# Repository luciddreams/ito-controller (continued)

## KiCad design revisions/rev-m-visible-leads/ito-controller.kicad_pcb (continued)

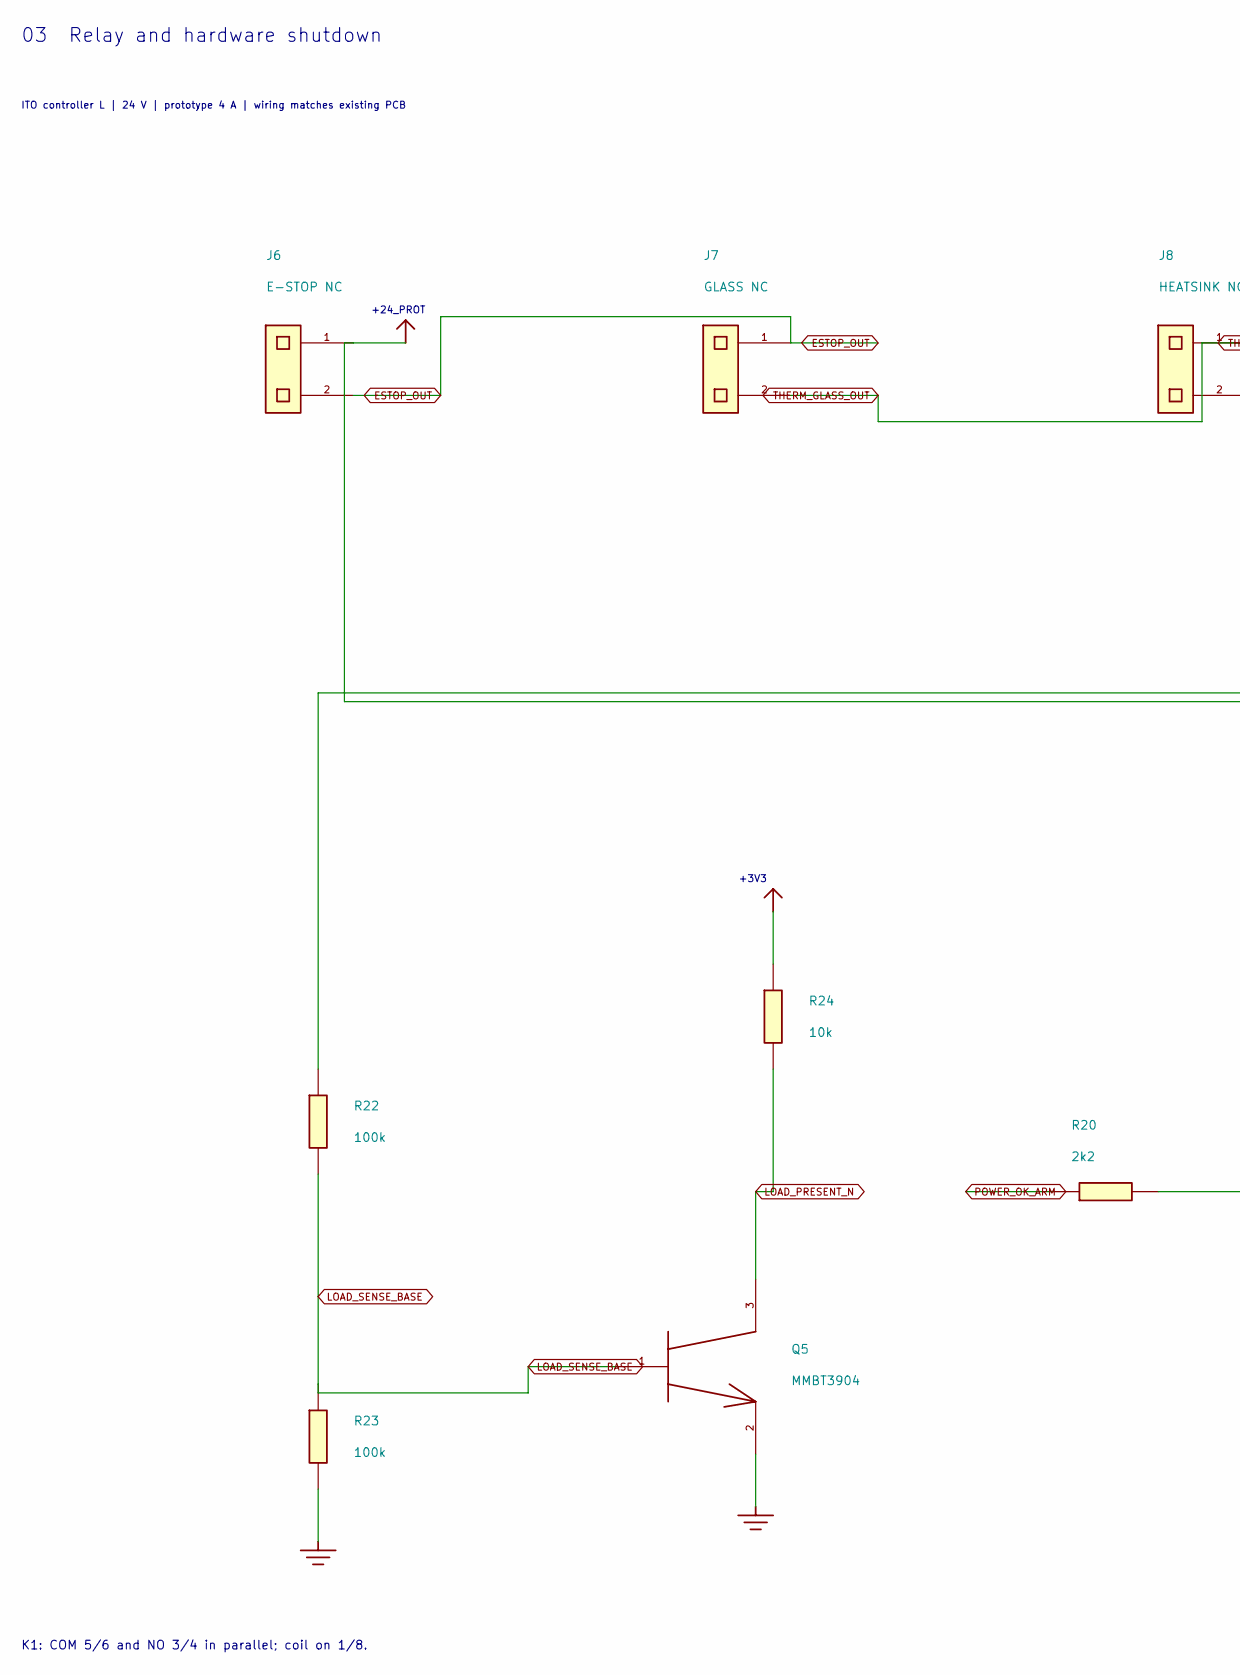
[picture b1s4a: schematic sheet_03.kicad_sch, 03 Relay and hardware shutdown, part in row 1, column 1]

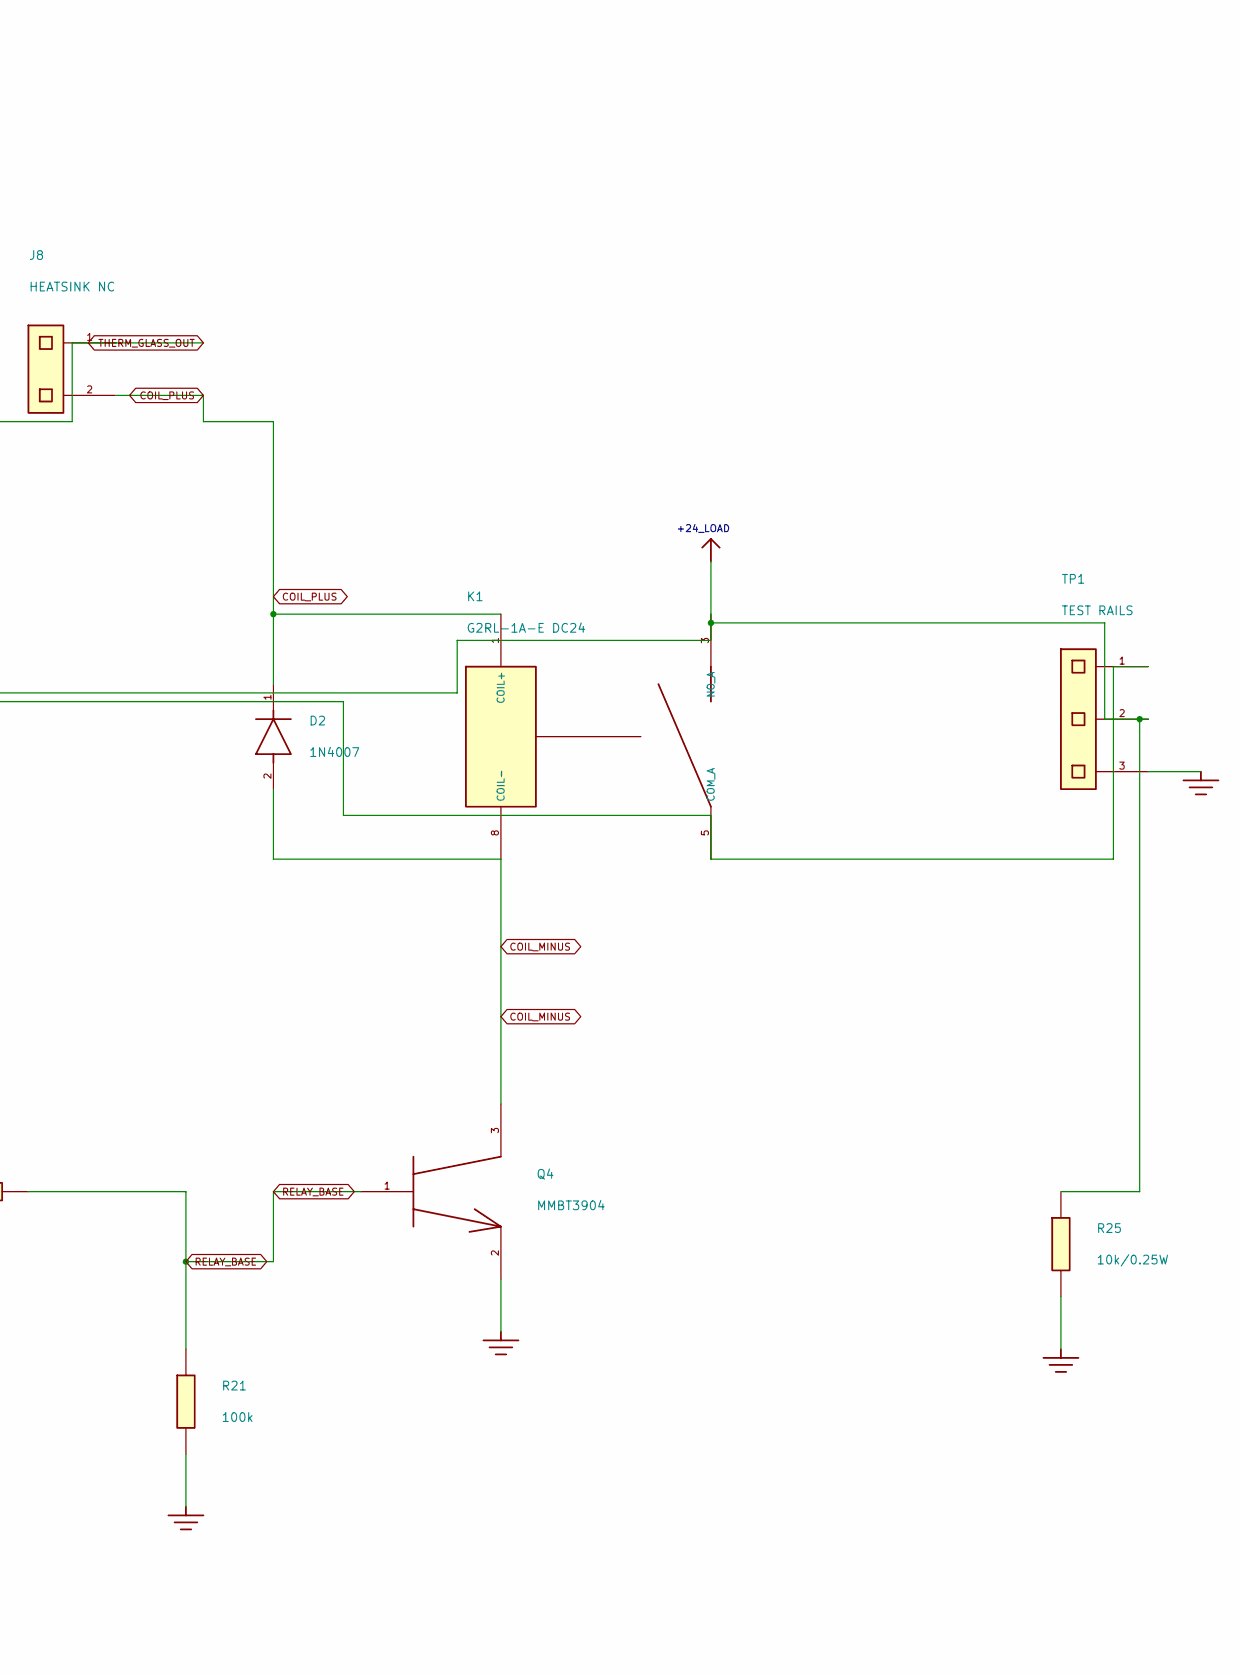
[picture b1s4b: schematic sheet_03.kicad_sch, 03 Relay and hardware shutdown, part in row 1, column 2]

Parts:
D2: 1N4007; D_DO-41_SOD81_P10.16mm_Horizontal; MPN 1N4007-E3/54
J6, J7, J8: Connector 2 pins; JST_XH_B2B-XH-A_1x02_P2.50mm_Vertical; MPN B2B-XH-A(LF)(SN)
K1: G2RL-1A-E DC24; G2RL_1A_E_review; MPN G2RL-1A-E DC24
Q4, Q5: MMBT3904; SOT-23; MPN MMBT3904LT1G
R20: 2k2; R_0805_2012Metric; MPN RC0805FR-072K2L
R21, R22, R23: 100k; R_0805_2012Metric; MPN RC0805FR-07100KL
R24: 10k; R_0805_2012Metric; MPN RC0805FR-0710KL
R25: 10k / 0.25W; R_0805_2012Metric; MPN ERJP06F1002V
TP1: Connector 3 pins; PinHeader_1x03_P2.54mm_Vertical; MPN TSW-103-07-G-S

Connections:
+3V3: R24.1; also elsewhere on the board
+24_LOAD: K1.3 (NO_A), K1.4 (NO_B), R22.1, R25.1, TP1.2; also elsewhere on the board
+24_PROT: J6.1, K1.5 (COM_A), K1.6 (COM_B), TP1.1; also elsewhere on the board
COIL_MINUS: D2.2, K1.8 (COIL-), Q4.3
COIL_PLUS: D2.1, J8.2, K1.1 (COIL+)
ESTOP_OUT: J6.2, J7.1
GND: Q4.2, Q5.2, R21.2, R23.2, R25.2, TP1.3; also elsewhere on the board
LOAD_PRESENT_N: Q5.3, R24.2; also elsewhere on the board
LOAD_SENSE_BASE: Q5.1, R22.2, R23.1
POWER_OK_ARM: R20.1; also elsewhere on the board
RELAY_BASE: Q4.1, R20.2, R21.1
THERM_GLASS_OUT: J7.2, J8.1

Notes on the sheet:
K1: COM 5/6 and NO 3/4 in parallel; coil on 1/8.
+24_PROT
+24_LOAD
+3V3
03 Relay and hardware shutdown
ITO controller L | 24 V | prototype 4 A | wiring matches existing PCB

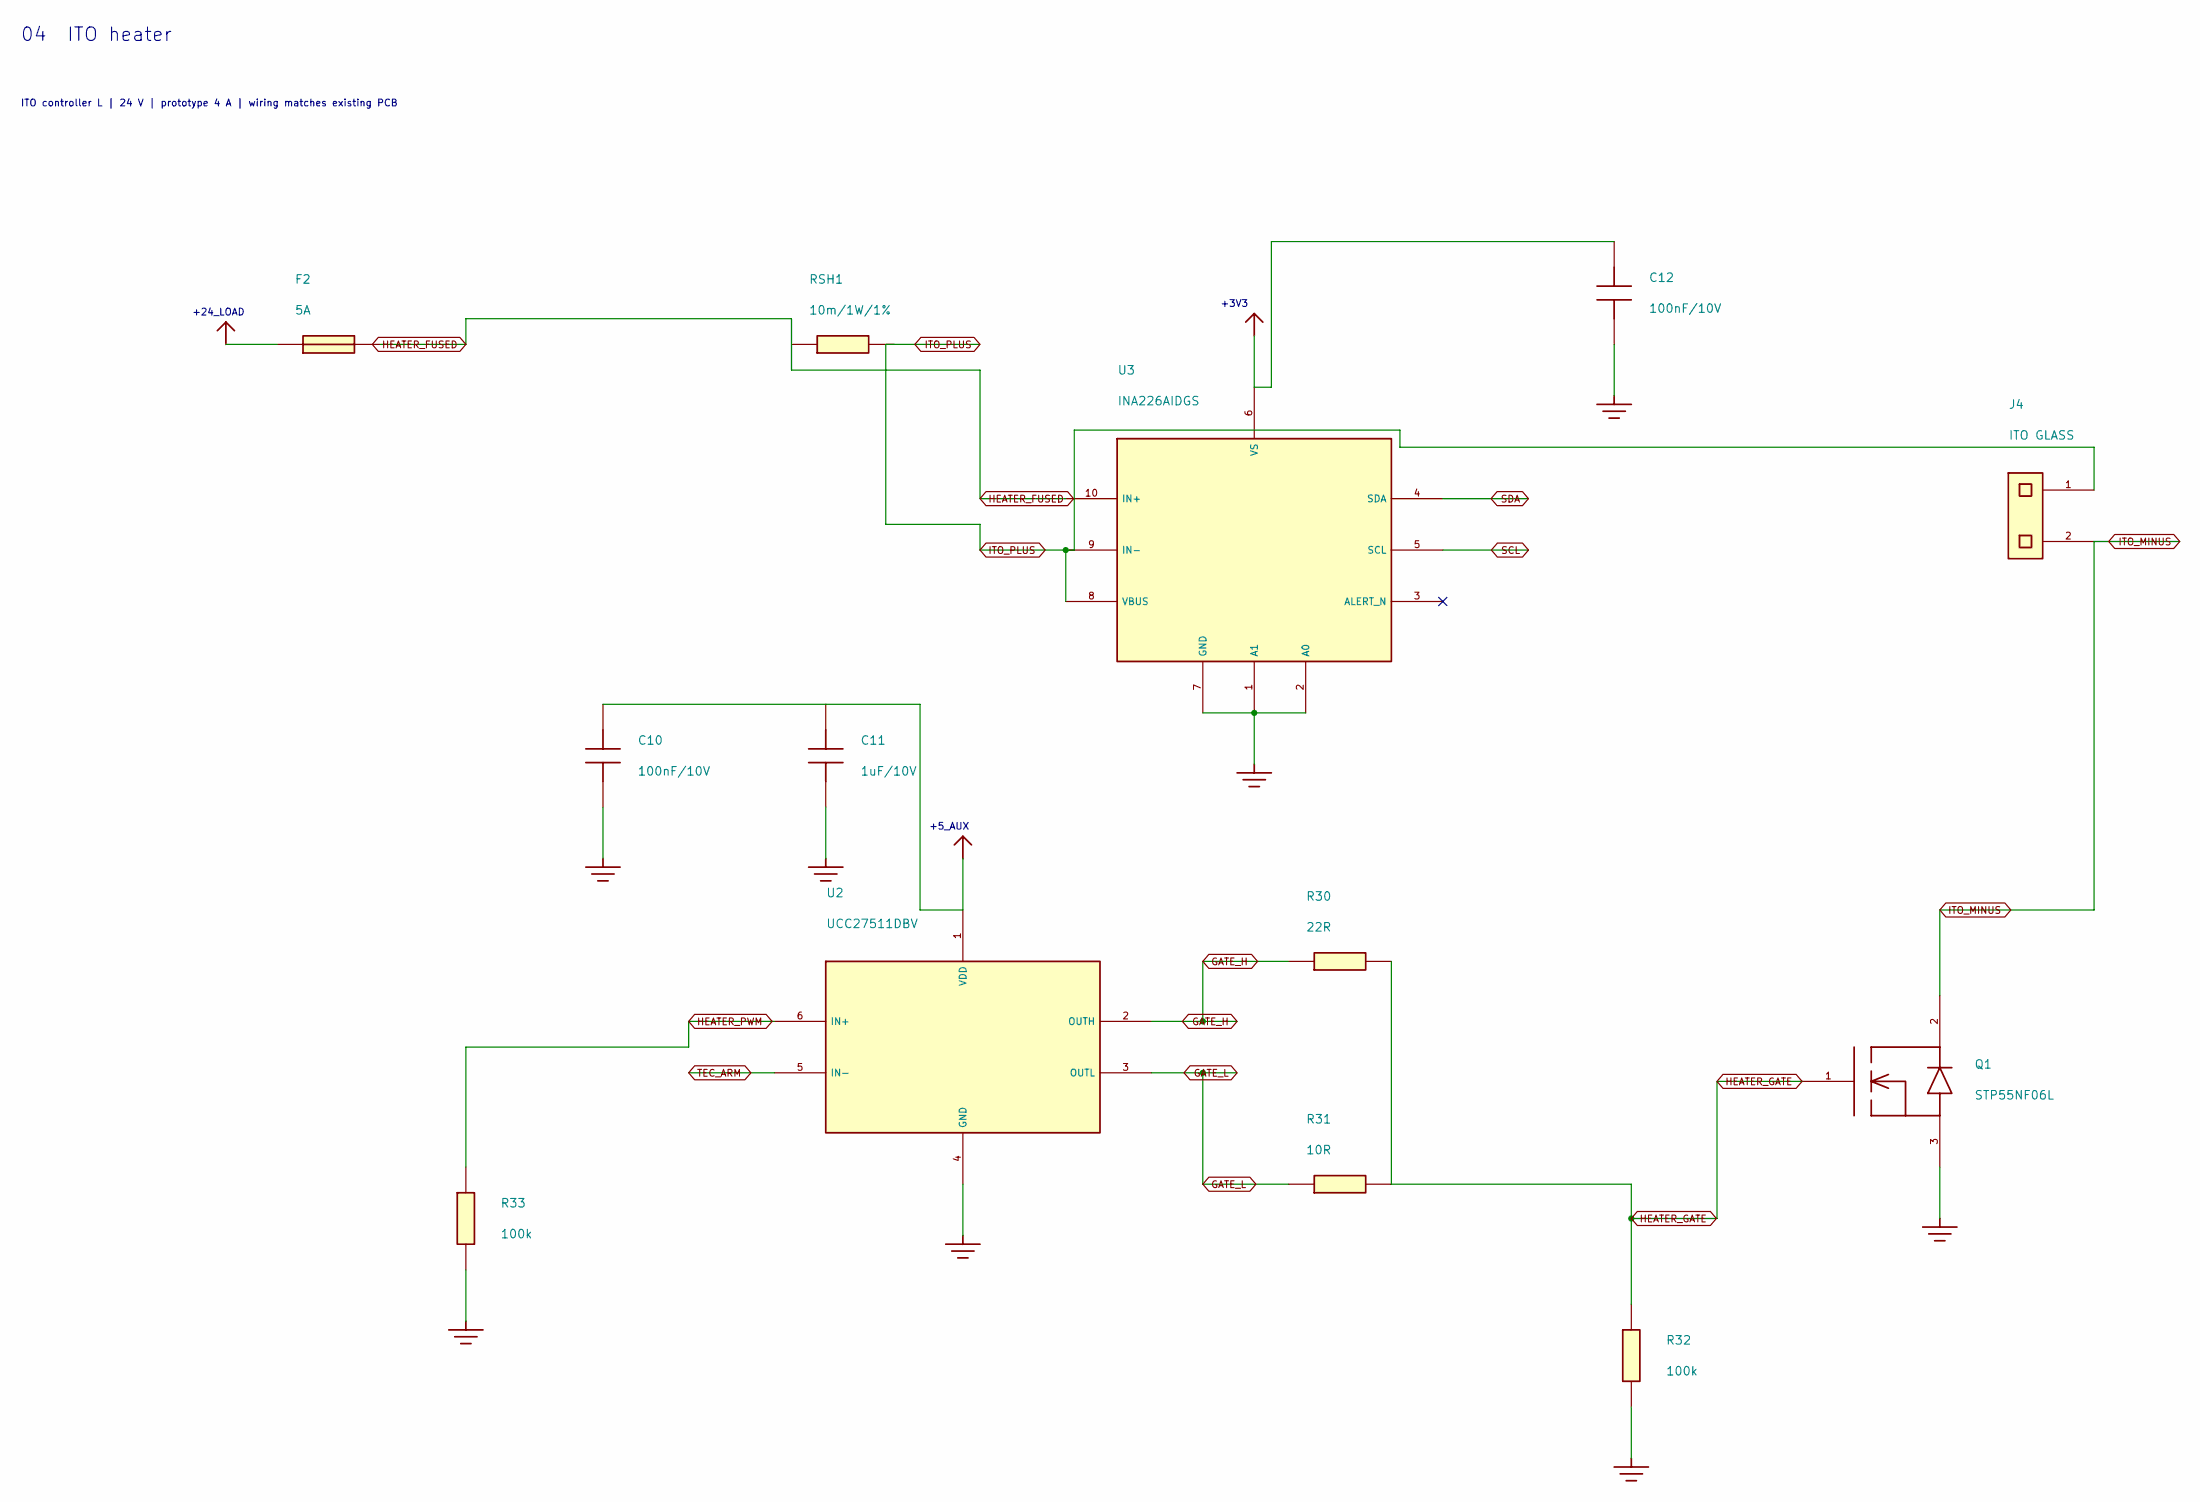
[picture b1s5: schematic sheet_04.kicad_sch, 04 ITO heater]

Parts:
C10, C12: 100n / 10V; C_0805_2012Metric; MPN GRM21BR71H104KA01L
C11: 1u / 10V; C_0805_2012Metric; MPN GRM21BR71H105KA12L
F2: 5A / 125V DC 0451005.MRL; Littelfuse_451; MPN 0451005.MRL
J4: Connector 2 pins; TerminalBlock_Phoenix_MKDS-1,5-2-5.08_1x02_P5.08mm_Horizont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; MPN 1715721
Q1: STP55NF06L; TO-220-3_Vertical; MPN STP55NF06L
R30: 22R; R_0805_2012Metric; MPN RC0805FR-0722RL
R31: 10R; R_0805_2012Metric; MPN RC0805FR-0710RL
R32, R33: 100k; R_0805_2012Metric; MPN RC0805FR-07100KL
RSH1: 10m / 1W / 1% WSL2512R0100FEA; WSL2512_7m_to_500m; MPN WSL2512R0100FEA
U2: UCC27511DBV; SOT-23-6; MPN UCC27511DBVR
U3: INA226AIDGS; VSSOP-10_3x3mm_P0.5mm; MPN INA226AIDGSR

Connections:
+3V3: C12.1, U3.6 (VS); also elsewhere on the board
+5_AUX: C10.1, C11.1, U2.1 (VDD); also elsewhere on the board
+24_LOAD: F2.1; also elsewhere on the board
GATE_H: R30.1, U2.2 (OUTH)
GATE_L: R31.1, U2.3 (OUTL)
GND: C10.2, C11.2, C12.2, Q1.3, R32.2, R33.2, U2.4 (GND), U3.1 (A1), U3.2 (A0), U3.7 (GND); also elsewhere on the board
HEATER_FUSED: F2.2, RSH1.1, U3.10 (IN+)
HEATER_GATE: Q1.1, R30.2, R31.2, R32.1
HEATER_PWM: R33.1, U2.6 (IN+); also elsewhere on the board
ITO_MINUS: J4.2, Q1.2
ITO_PLUS: J4.1, RSH1.2, U3.8 (VBUS), U3.9 (IN-)
SCL: U3.5 (SCL); also elsewhere on the board
SDA: U3.4 (SDA); also elsewhere on the board
TEC_ARM: U2.5 (IN-); also elsewhere on the board

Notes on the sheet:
+24_LOAD
+5_AUX
+3V3
04 ITO heater
ITO controller L | 24 V | prototype 4 A | wiring matches existing PCB

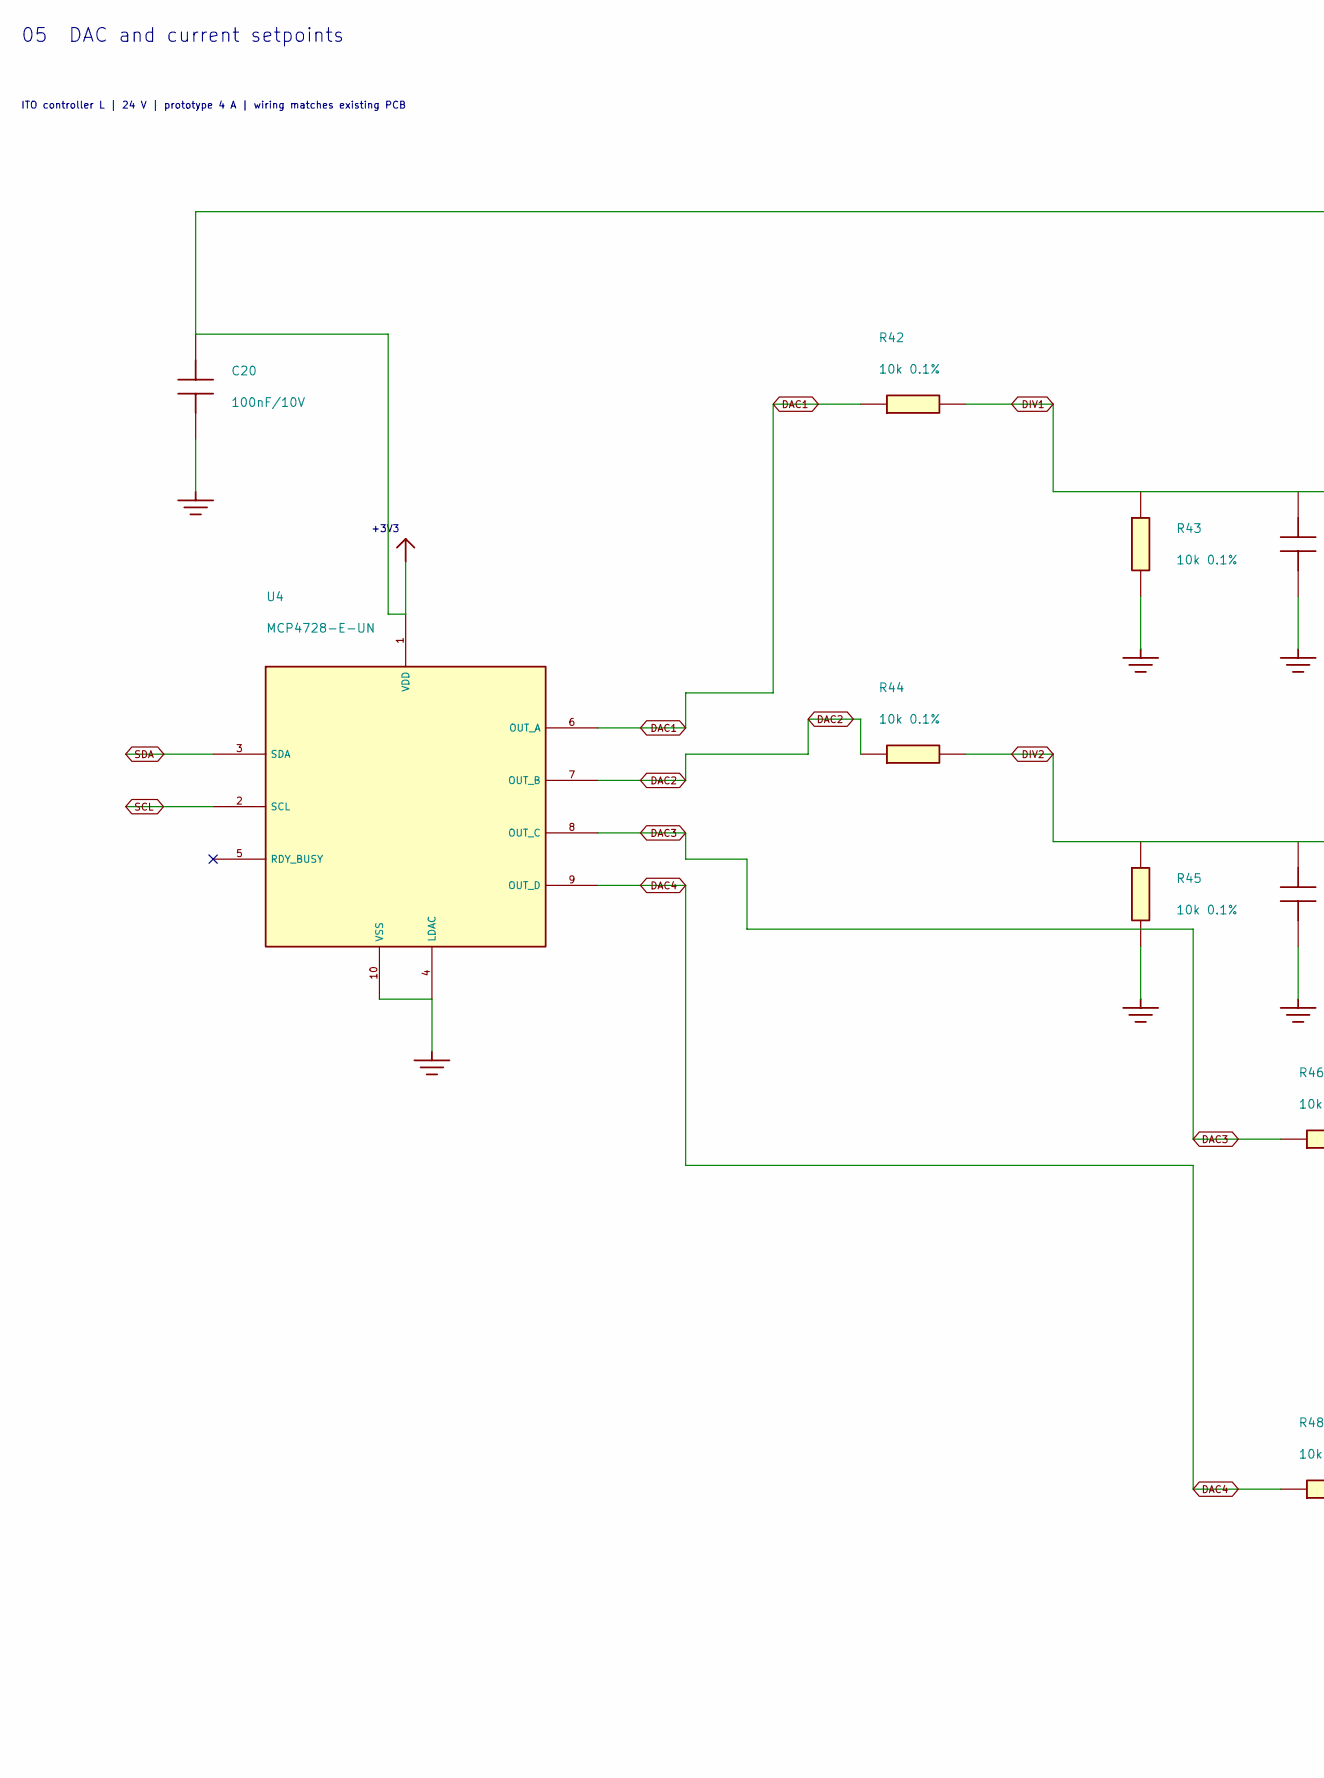
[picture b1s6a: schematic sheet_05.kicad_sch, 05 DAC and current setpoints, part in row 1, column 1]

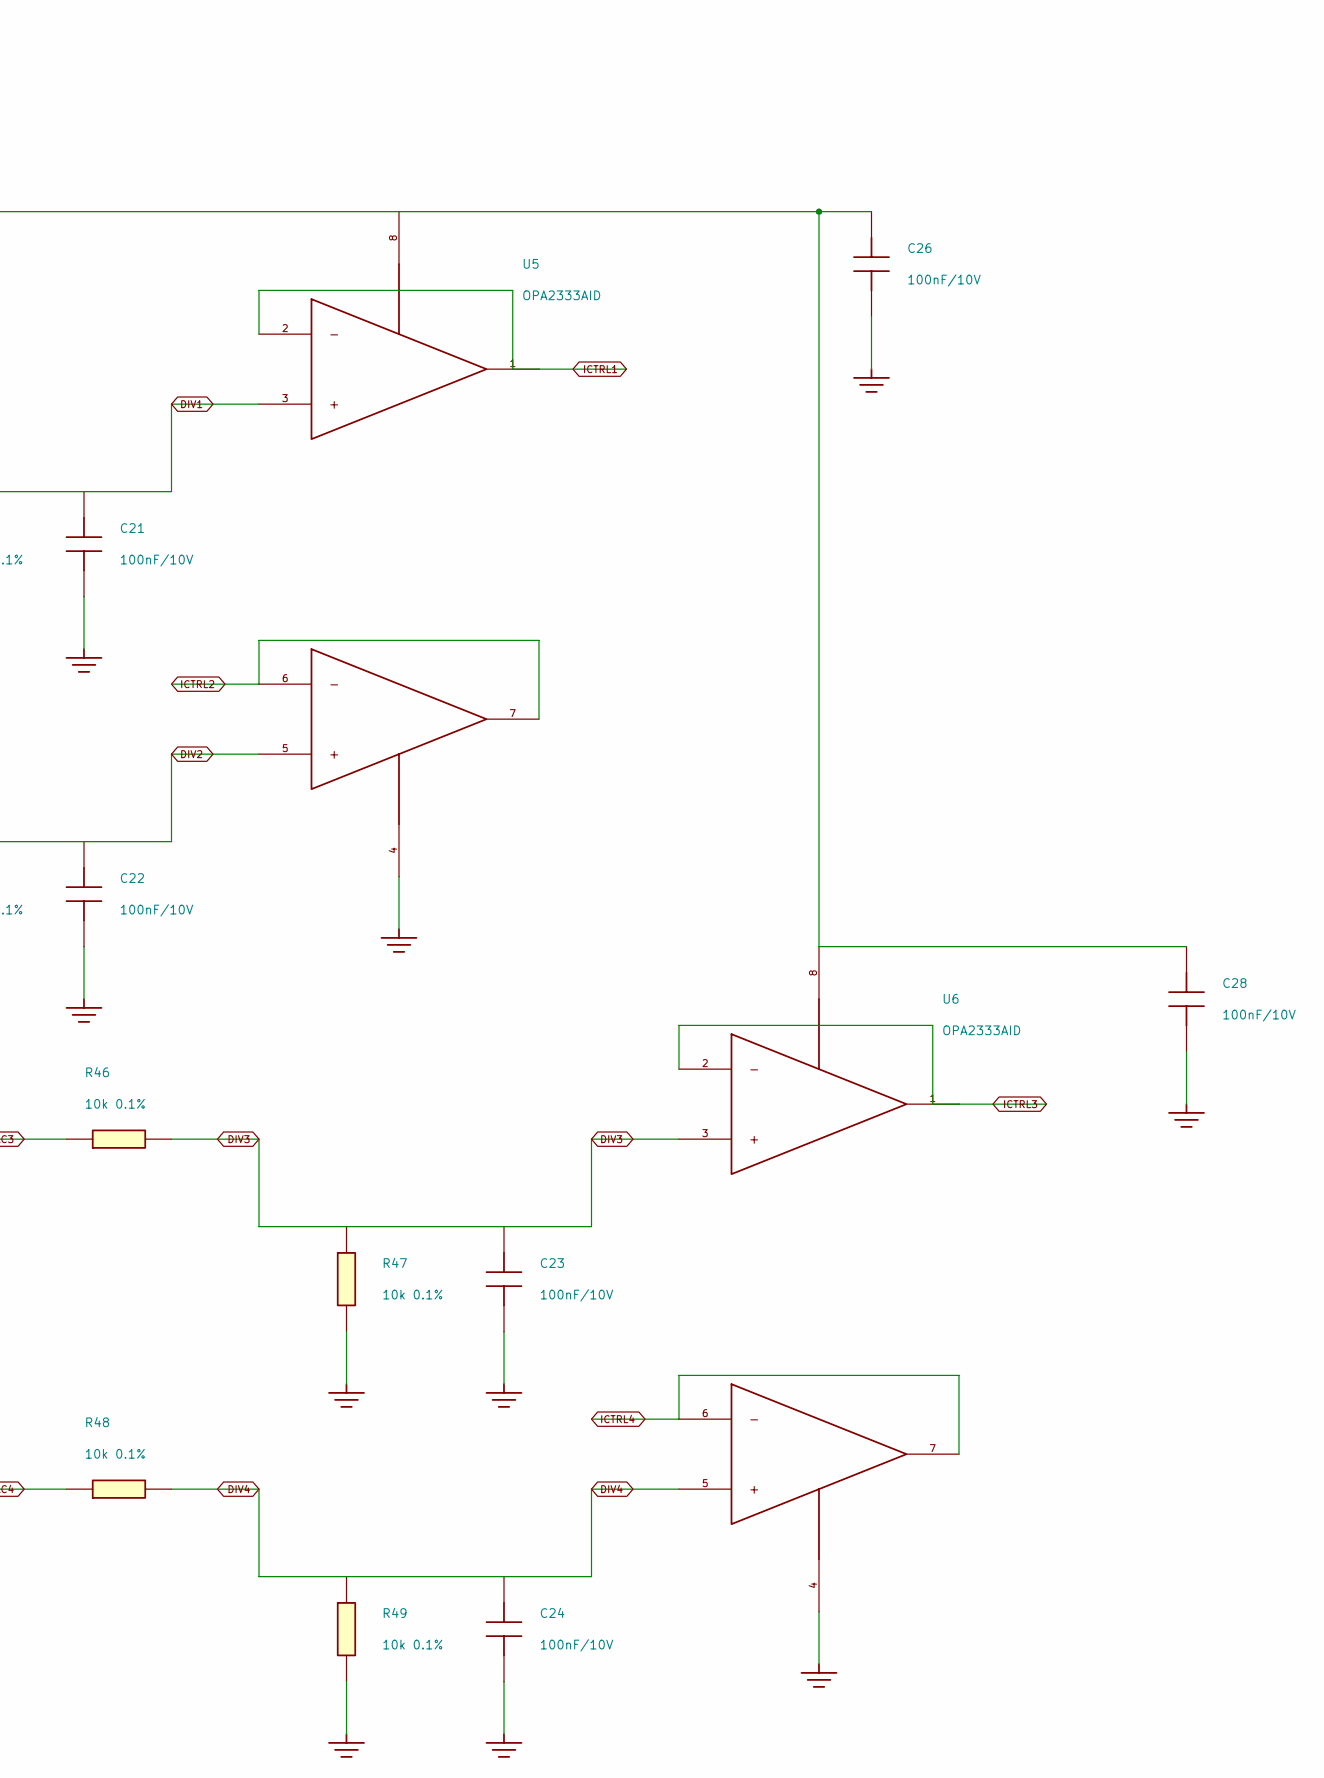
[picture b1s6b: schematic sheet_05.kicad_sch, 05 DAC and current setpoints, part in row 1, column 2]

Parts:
C20, C21, C22, C23, C24, C26, C28: 100n / 10V; C_0805_2012Metric; MPN GRM21BR71H104KA01L
R42, R44, R46, R48: 4k02 0.1%; R_0805_2012Metric; MPN RT0805BRD0710KL
R43, R45, R47, R49: 10k 0.1%; R_0805_2012Metric; MPN RT0805BRD0710KL
U4: MCP4728-E-UN; MSOP-10_3x3mm_P0.5mm; MPN MCP4728-E/UN
U5, U6: OPA2333AID; SOIC-8_3.9x4.9mm_P1.27mm; MPN OPA2333AIDR

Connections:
+3V3: C20.1, C26.1, C28.1, U4.1 (VDD), U5.8 (V+), U6.8 (V+); also elsewhere on the board
DAC1: R42.1, U4.6 (OUT_A)
DAC2: R44.1, U4.7 (OUT_B)
DAC3: R46.1, U4.8 (OUT_C)
DAC4: R48.1, U4.9 (OUT_D)
DIV1: C21.1, R42.2, R43.1, U5.3 (IN+_A)
DIV2: C22.1, R44.2, R45.1, U5.5 (IN+_B)
DIV3: C23.1, R46.2, R47.1, U6.3 (IN+_A)
DIV4: C24.1, R48.2, R49.1, U6.5 (IN+_B)
GND: C20.2, C21.2, C22.2, C23.2, C24.2, C26.2, C28.2, R43.2, R45.2, R47.2, R49.2, U4.4 (LDAC), U4.10 (VSS), U5.4 (V-), U6.4 (V-); also elsewhere on the board
ICTRL1: U5.1 (OUT_A), U5.2 (IN-_A); also elsewhere on the board
ICTRL2: U5.6 (IN-_B), U5.7 (OUT_B); also elsewhere on the board
ICTRL3: U6.1 (OUT_A), U6.2 (IN-_A); also elsewhere on the board
ICTRL4: U6.6 (IN-_B), U6.7 (OUT_B); also elsewhere on the board
SCL: U4.2 (SCL); also elsewhere on the board
SDA: U4.3 (SDA); also elsewhere on the board

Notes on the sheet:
+3V3
05 DAC and current setpoints
ITO controller L | 24 V | prototype 4 A | wiring matches existing PCB

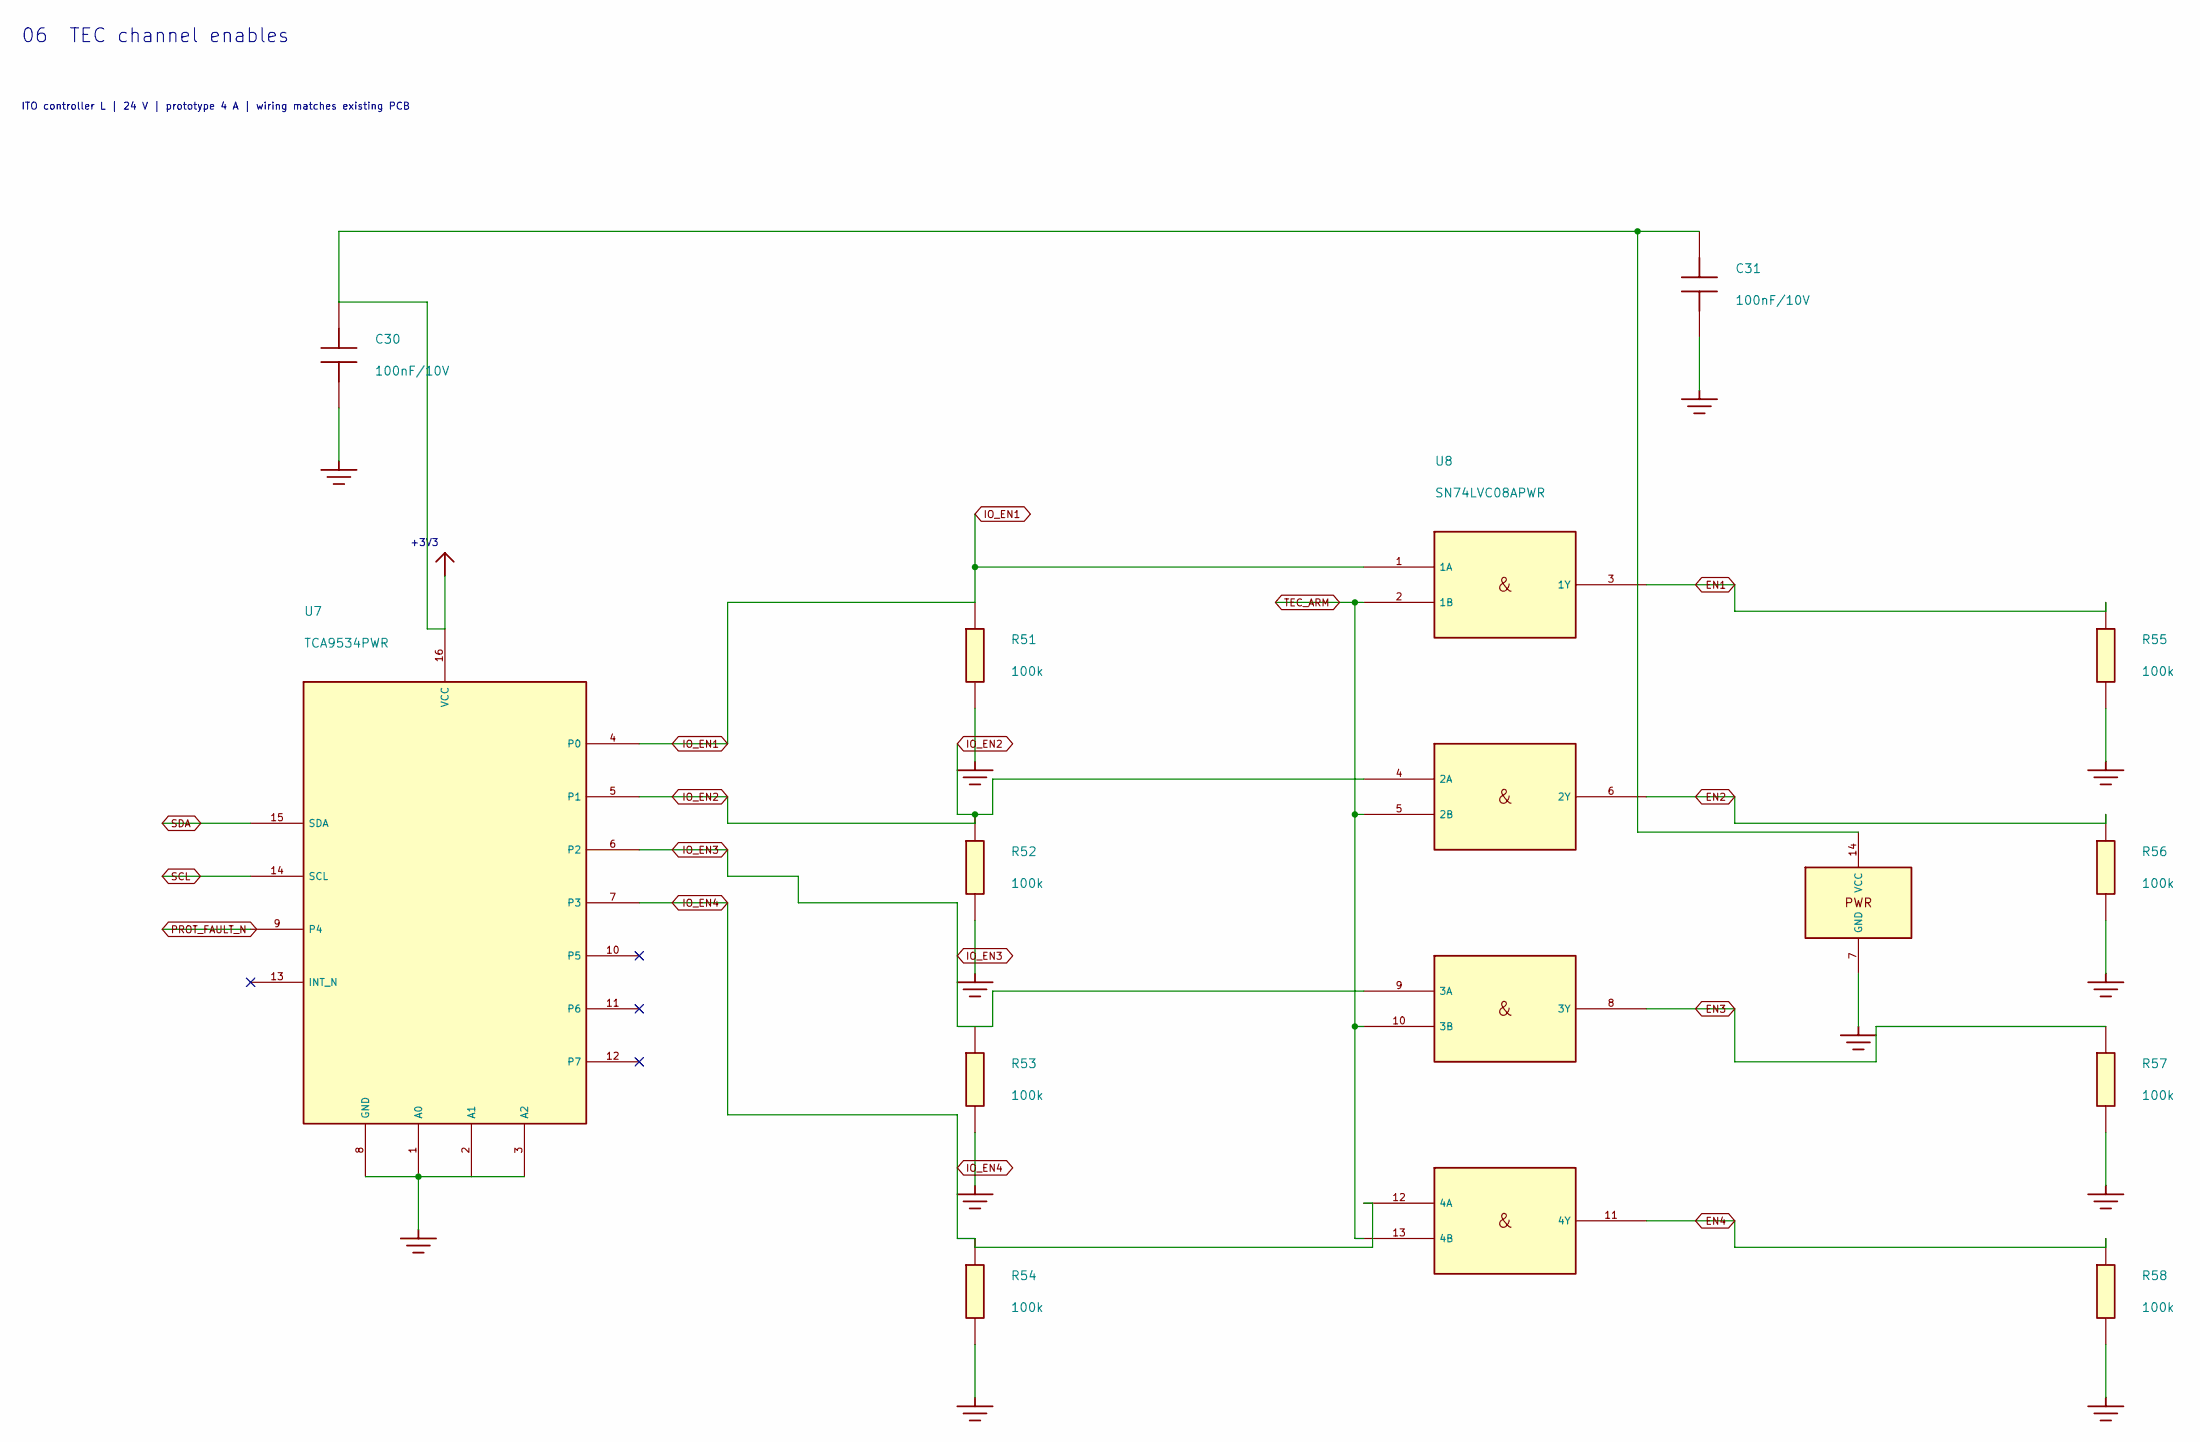
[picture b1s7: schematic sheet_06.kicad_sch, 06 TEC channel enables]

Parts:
C30, C31: 100n / 10V; C_0805_2012Metric; MPN GRM21BR71H104KA01L
R51, R52, R53, R54, R55, R56, R57, R58: 100k; R_0805_2012Metric; MPN RC0805FR-07100KL
U7: TCA9534PWR; TSSOP-16_4.4x5mm_P0.65mm; MPN TCA9534PWR
U8: SN74LVC08APWR; TSSOP-14_4.4x5mm_P0.65mm; MPN SN74LVC08APWR

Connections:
+3V3: C30.1, C31.1, U7.16 (VCC), U8.14 (VCC); also elsewhere on the board
EN1: R55.1, U8.3 (1Y); also elsewhere on the board
EN2: R56.1, U8.6 (2Y); also elsewhere on the board
EN3: R57.1, U8.8 (3Y); also elsewhere on the board
EN4: R58.1, U8.11 (4Y); also elsewhere on the board
GND: C30.2, C31.2, R51.2, R52.2, R53.2, R54.2, R55.2, R56.2, R57.2, R58.2, U7.1 (A0), U7.2 (A1), U7.3 (A2), U7.8 (GND), U8.7 (GND); also elsewhere on the board
IO_EN1: R51.1, U7.4 (P0), U8.1 (1A)
IO_EN2: R52.1, U7.5 (P1), U8.4 (2A)
IO_EN3: R53.1, U7.6 (P2), U8.9 (3A)
IO_EN4: R54.1, U7.7 (P3), U8.12 (4A)
PROT_FAULT_N: U7.9 (P4); also elsewhere on the board
SCL: U7.14 (SCL); also elsewhere on the board
SDA: U7.15 (SDA); also elsewhere on the board
TEC_ARM: U8.2 (1B), U8.5 (2B), U8.10 (3B), U8.13 (4B); also elsewhere on the board

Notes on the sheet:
+3V3
06 TEC channel enables
ITO controller L | 24 V | prototype 4 A | wiring matches existing PCB
